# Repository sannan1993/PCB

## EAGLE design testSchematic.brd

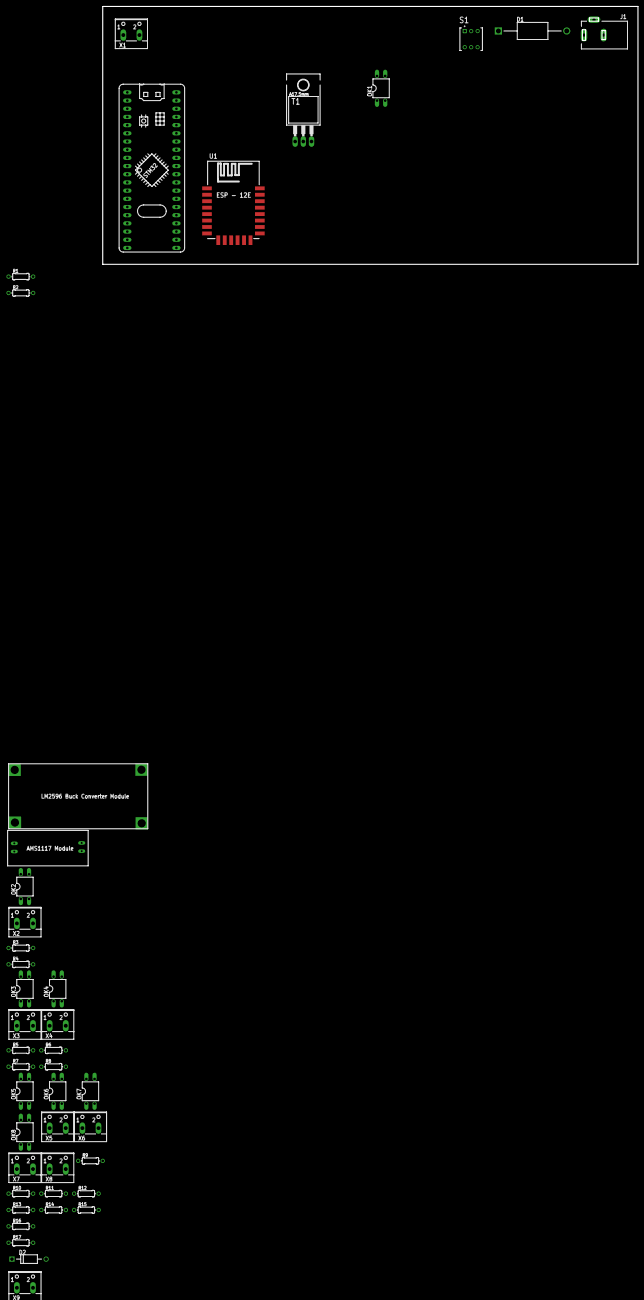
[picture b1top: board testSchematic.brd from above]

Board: 2 copper layers, 166.0 x 80.0 mm, 43 parts (0 on the bottom side), 25 nets, no tracks yet.

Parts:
D1: 1N5822; DIOAD2120W130L950D530P
D2: 1N4007; DIOAD1060W80L520D270
J1: DCJ0303
OK1, OK2, OK3, OK4, OK5, OK6, OK7, OK8: PC817; DIL04
R1, R2, R3, R4, R5, R6, R7, R8, R9, R10, R11, R12, R13, R14, R15, R16, R17: 0204/7
S1: TL2230OAF140; SW_TL2230OAF140
T1: TIP122; TO220
U1: ESP12ESMD; ESP12E-SMD
U$1: BLUE_PILL
U$2: LM2596_MODULE
U$3: AMS1117_MODULE
X1, X2, X3, X4, X5, X6, X7, X8, X9: W237-102

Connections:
+3V3: R2.1, R4.1, R6.1, R8.1, R10.1, R12.1, R14.1, R16.1, U$3.VOUT+
+5V: U$2.OUT+, U$3.VIN+
+12V: D2.C, S1.2, U$2.IN+, X1.1, X2.1, X3.1, X4.1, X5.1, X6.1, X7.1, X8.1, X9.2
GND: J1.2, J1.3, OK1.2, OK1.3, OK2.2, OK2.3, OK3.2, OK3.3, OK4.2, OK4.3, OK5.2, OK5.3, OK6.2, OK6.3, OK7.2, OK7.3, OK8.2, OK8.3, T1.3, U$2.IN-, U$2.OUT-, U$3.GND, U$3.GND-
unnamed: D1.A, J1.1
unnamed: D1.C, S1.3
unnamed: OK2.1, R3.1
unnamed: R3.2, X2.2
unnamed: OK1.1, R1.1
unnamed: OK3.1, R5.1
unnamed: R5.2, X3.2
unnamed: OK4.1, R7.1
unnamed: R7.2, X4.2
unnamed: OK5.1, R9.1
unnamed: R9.2, X5.2
unnamed: OK6.1, R11.1
unnamed: R11.2, X6.2
unnamed: OK7.1, R13.1
unnamed: R13.2, X7.2
unnamed: OK8.1, R15.1
unnamed: R15.2, X8.2
unnamed: R17.1, T1.1
unnamed: D2.A, T1.2, X9.1
unnamed: R1.2, X1.2
UCTLR_PIN_: OK1.4, OK2.4, OK3.4, OK4.4, OK5.4, OK6.4, OK7.4, OK8.4, R2.2, R4.2, R6.2, R8.2, R10.2, R12.2, R14.2, R16.2

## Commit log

2023-08-31 esp connectivity
